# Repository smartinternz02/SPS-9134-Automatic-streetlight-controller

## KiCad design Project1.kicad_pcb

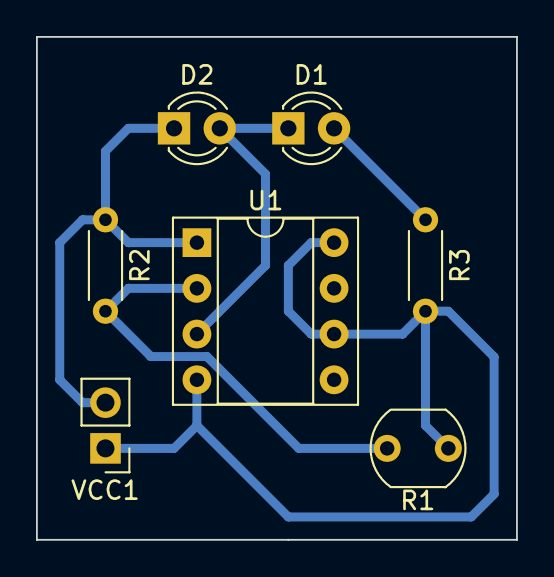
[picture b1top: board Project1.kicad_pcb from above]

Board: 2 copper layers, 26.7 x 27.9 mm, 7 parts (0 on the bottom side), 5 nets.

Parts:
D1, D2: LED; LED_D3.0mm
R1: LDR07; R_LDR_5.1x4.3mm_P3.4mm_Vertical
R2: 47K; R_Axial_DIN0204_L3.6mm_D1.6mm_P5.08mm_Horizontal
R3: 330E; R_Axial_DIN0204_L3.6mm_D1.6mm_P5.08mm_Horizontal
U1: LM555; DIP-8_W7.62mm_Socket
VCC1: DC 9; PinHeader_1x02_P2.54mm_Vertical

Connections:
GND: D2.1, R2.1, U1.1, VCC1.2
unnamed: D1.1, D2.2, U1.3
unnamed: D1.2, R3.1
unnamed: R1.1, R3.2, U1.4, U1.6, U1.8, VCC1.1
unnamed: R1.2, R2.2, U1.2

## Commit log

2021-03-24 Create Final Video Link
